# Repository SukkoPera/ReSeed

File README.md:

# ReSeed

ReSeed is an expansion card for the Commodore 16 and Plus/4 computers that allows interfacing the computer with a [MOS 6581 or 8580 Sound Interface Device](https://en.wikipedia.org/wiki/MOS_Technology_6581), the chip that is used to deliver audio on the Commodore 64.

It is based on [a design by Solder of Synergy](https://plus4world.powweb.com/hardware/Solders_SID_Card).

## Summary
Sounds from the C64 now for the Plus/4! Just plug the card into the Expansion Port! You can adjust the volume on the card. You can hear the sound over the Plus/4 audio or take it over a 3.5mm-Stereo-Cinch to a mixer or HiFi-Device. A 9-pin D-SUB connector allows connecting a 3<sup>rd</sup> (analog!) joystick or a proportional-mouse or (why not?) paddles!

*(Slight rewording of Solder's original description of the card.)*

## Design
ReSeed is derived from Solder's SIDcard, with a few enhancements.

### Modifications Introduced in V2
The focus for V2 was on reducing the output noise.

* New component values for the step-up voltage regulator: The values of some components were fine-tuned (again) in order to place the switching frequency of the step-up voltage converter way out of the audio band. These new values can also be retrofitted on a V1 board and will improve things dramatically (See [V1.1](https://github.com/SukkoPera/ReSeed/releases/tag/v1.1)).
* Alternative voltage step-up module: Cheap step-up voltage boost modules can now be used instead of the TL497-based circuit. Such modules, which can be easily sourced from Chinese portals, are much more modern and use a higher switching frequency, resulting in (near-)zero switching-induced noise. Using them also speeds up the assembly process, as many components can be skipped.
* Linear Regulator: If you are really paranoid about switching-induced noise, you can use the above alternatives as a first-stage voltage regulator and then make a second stage through a linear regulator, which should "eat" any remaining noise and provide the SID with very stable power.
* Separate grounds: A separate audio ground plane was introduced and connected to the signal ground plane through a single ferrite bead, preventing noise from spreading from the latter to the former. A second ferrite bead was inserted on the incoming +5V power rail in order to make it cleaner.
* Alternative BJT footprint: An alternative footprint for the output amplifier transistor was added, allowing for the mounting of the 2SC1815 BJT used in the original C64 audio circuit.
* SID clock delay circuit: This allows use of CD74HCT4520B chips in place of the CD4520B.
* Clock divider reset: Makes sure the SID clock always has the correct phase upon startup/reset.
* Short-circuit protection: In the original Solder design, a short-circuit can happen on the joystick port if it is written to. Series resistors were added in order to avoid this situation.

### Modifications Introduced in [V1](https://github.com/SukkoPera/ReSeed/releases/tag/v1)
* Supports both MOS 6581 and 8580 SIDs: this depends on mounting different components though, the board **cannot** be switched "on-the-fly", see [below](#Assembly).
* A volume control for the DigiFix was added and even a switch to completely bypass it.
* The output switch was removed: audio is automatically redirected to the Plus/4's EXT_AUDIO when nothing is connected to the output jack.
* The second stage of the amplifier was removed and the first stage modified so that it uses the same circuit and component values as the C64: the original card was known to introduce some distortion to the output signal as it was trying to amplify it, these days you can easily do better amplification outboard, so we chose to preserve sound fidelity.
* A decoupling capacitor was added close to every IC.
* The values for the step-up converter were recalculated in order to make the generated voltage less noisy and as ripple-free as possible.
* Last but not least, the design was documented and made open.

## Assembly
If you want to assemble a card, **please read the assembly notes on [the Wiki](https://github.com/SukkoPera/ReSeed/wiki) carefully or you might destroy your SID chip!**

### SID Replacements
Most SID replacements will not work correctly. This is because for technical reasons the clock that is provided to the SID has a lower frequency than what it gets on the C64 (~886 vs ~985 kHz). Most SID replacements do not use this clock signal at all and just assume C64 frequency (I guess), leading to incorrect data transfers. This is the case for the SwinSID firmware, for instance.  See below for a table of tested SID replacement devices.

| SID Device | Compatibility | Source | Notes |
|:---:|:---:|:---:|:---|
| [ARMSID](https://www.nobomi.cz/8bit/armsid/index_en.php) | Yes | [Root42](https://www.youtube.com/watch?v=OQfjMYeEfFY) | May have subtle incompatibility (detected during porting of config tool to +4), but unlikely to be seen in practise. |
| [SIDKick](https://github.com/frntc/SIDKick-pico) | In Progress | [SIDKick Pico Github](https://github.com/frntc/SIDKick-pico/discussions/36) | |
| [SwinSID](https://github.com/dmantione/swinsid) | No | SukkoPera | One report of compatibility, but no evidence provided. |
| BackSID | No | [BackBit Forums](https://forum.backbit.io/index.php?topic=1089.0) | Discontinued closed-source product; firmware unlikely to be patched. |
| [KungFuSID](https://github.com/Sgw32/KungFuSID) | No | SukkoPera |  |
| [PD-SID](https://uni64.com/shop/index.php?system=4&m=70&item_id=7536) | No | SteveGuidi | Firmware v191; no sound output and USB port inhibits proper seating in socket (obstructed by socketed CD74HCT4520E). |

## Games & Software
You can get images of the disks Solder used to ship with his SIDcard [here](https://plus4world.powweb.com/software/Synergy_Sidcard_Software). These will help making sure that the card works as intended.

[Here is also a list](https://plus4world.powweb.com/effects/SID_Support) of a lot of C16/+4 games and software supporting the card.

## Releases
If you want to get this board produced, you are recommended to get [the latest release](https://github.com/SukkoPera/ReSeed/releases) rather than the current git version, as the latter might be under development and is not guaranteed to be working.

Every release is accompanied by its Bill Of Materials (BOM) file and any relevant notes about it, which you are recommended to read carefully.

## Enclosure
A 3D-printable enclosure is currently available for this board, it was kindly contributed by [Starquake](https://www.forum64.de/wcf/index.php?user/17096-starquake/) and it is available in the [enclosure](./enclosure) folder.

Usage should be self-explanatory, just note that there are two slightly different versions depending on the SID model, as the one for the 8580 has an extra hole in the upper shell for the Digifix). You will probably have to bend the ferrites and capacitor at the bottom of the board a little to the side.

2x countersunk head screws M3x5mm will be required for assembly.

Please see [this thread on Forum64](https://www.forum64.de/index.php?thread/138918-sammelbestellung-reseed-sid-cartridge-f%C3%BCr-plus-4-und-c16/&postID=2125424#post2125424) for more information and printing recommendations.

[SteveGuidi](https://github.com/SteveGuidi) kindly contributed original-264-style labels for the completed cartridge.

## License
The ReSeed documentation, including the design itself, is copyright &copy; SukkoPera 2022-2023 and is licensed under the [Creative Commons Attribution-NonCommercial-ShareAlike 4.0 International License](https://creativecommons.org/licenses/by-nc-sa/4.0/).

This documentation is distributed *as is* and WITHOUT ANY EXPRESS OR IMPLIED WARRANTIES whatsoever with respect to its functionality, operability or use, including, without limitation, any implied warranties OF MERCHANTABILITY, SATISFACTORY QUALITY, FITNESS FOR A PARTICULAR PURPOSE or infringement. We expressly disclaim any liability whatsoever for any direct, indirect, consequential, incidental or special damages, including, without limitation, lost revenues, lost profits, losses resulting from business interruption or loss of data, regardless of the form of action or legal theory under which the liability may be asserted, even if advised of the possibility or likelihood of such damages.

## Support the Project
If you want to get some boards manufactured, you can get them from PCBWay through this link:

You get my gratitude and cheap, professionally-made and good quality PCBs, I get some credit that will help with this and [other projects](https://www.pcbway.com/project/member/shareproject/?bmbid=41100). You won't even have to worry about the various PCB options, it's all pre-configured for you!

Also, if you still have to register, [you can use this link](https://www.pcbway.com/setinvite.aspx?inviteid=41100) to get some bonus initial credit (and yield me some more).

You can also buy me a coffee if you want:

## Thanks
- Solder, for designing the original card and sharing its schematics.
- [Kinmami](https://github.com/kinmami) for his invaluable support
- Luca, Chronos and all the folks at [Plus/4 World](https://plus4world.powweb.com/forum) for helping with the troubleshooting
- [thireo](https://github.com/thireo) for the [3D model of the headphone jack](https://github.com/thireo/kicad-library)

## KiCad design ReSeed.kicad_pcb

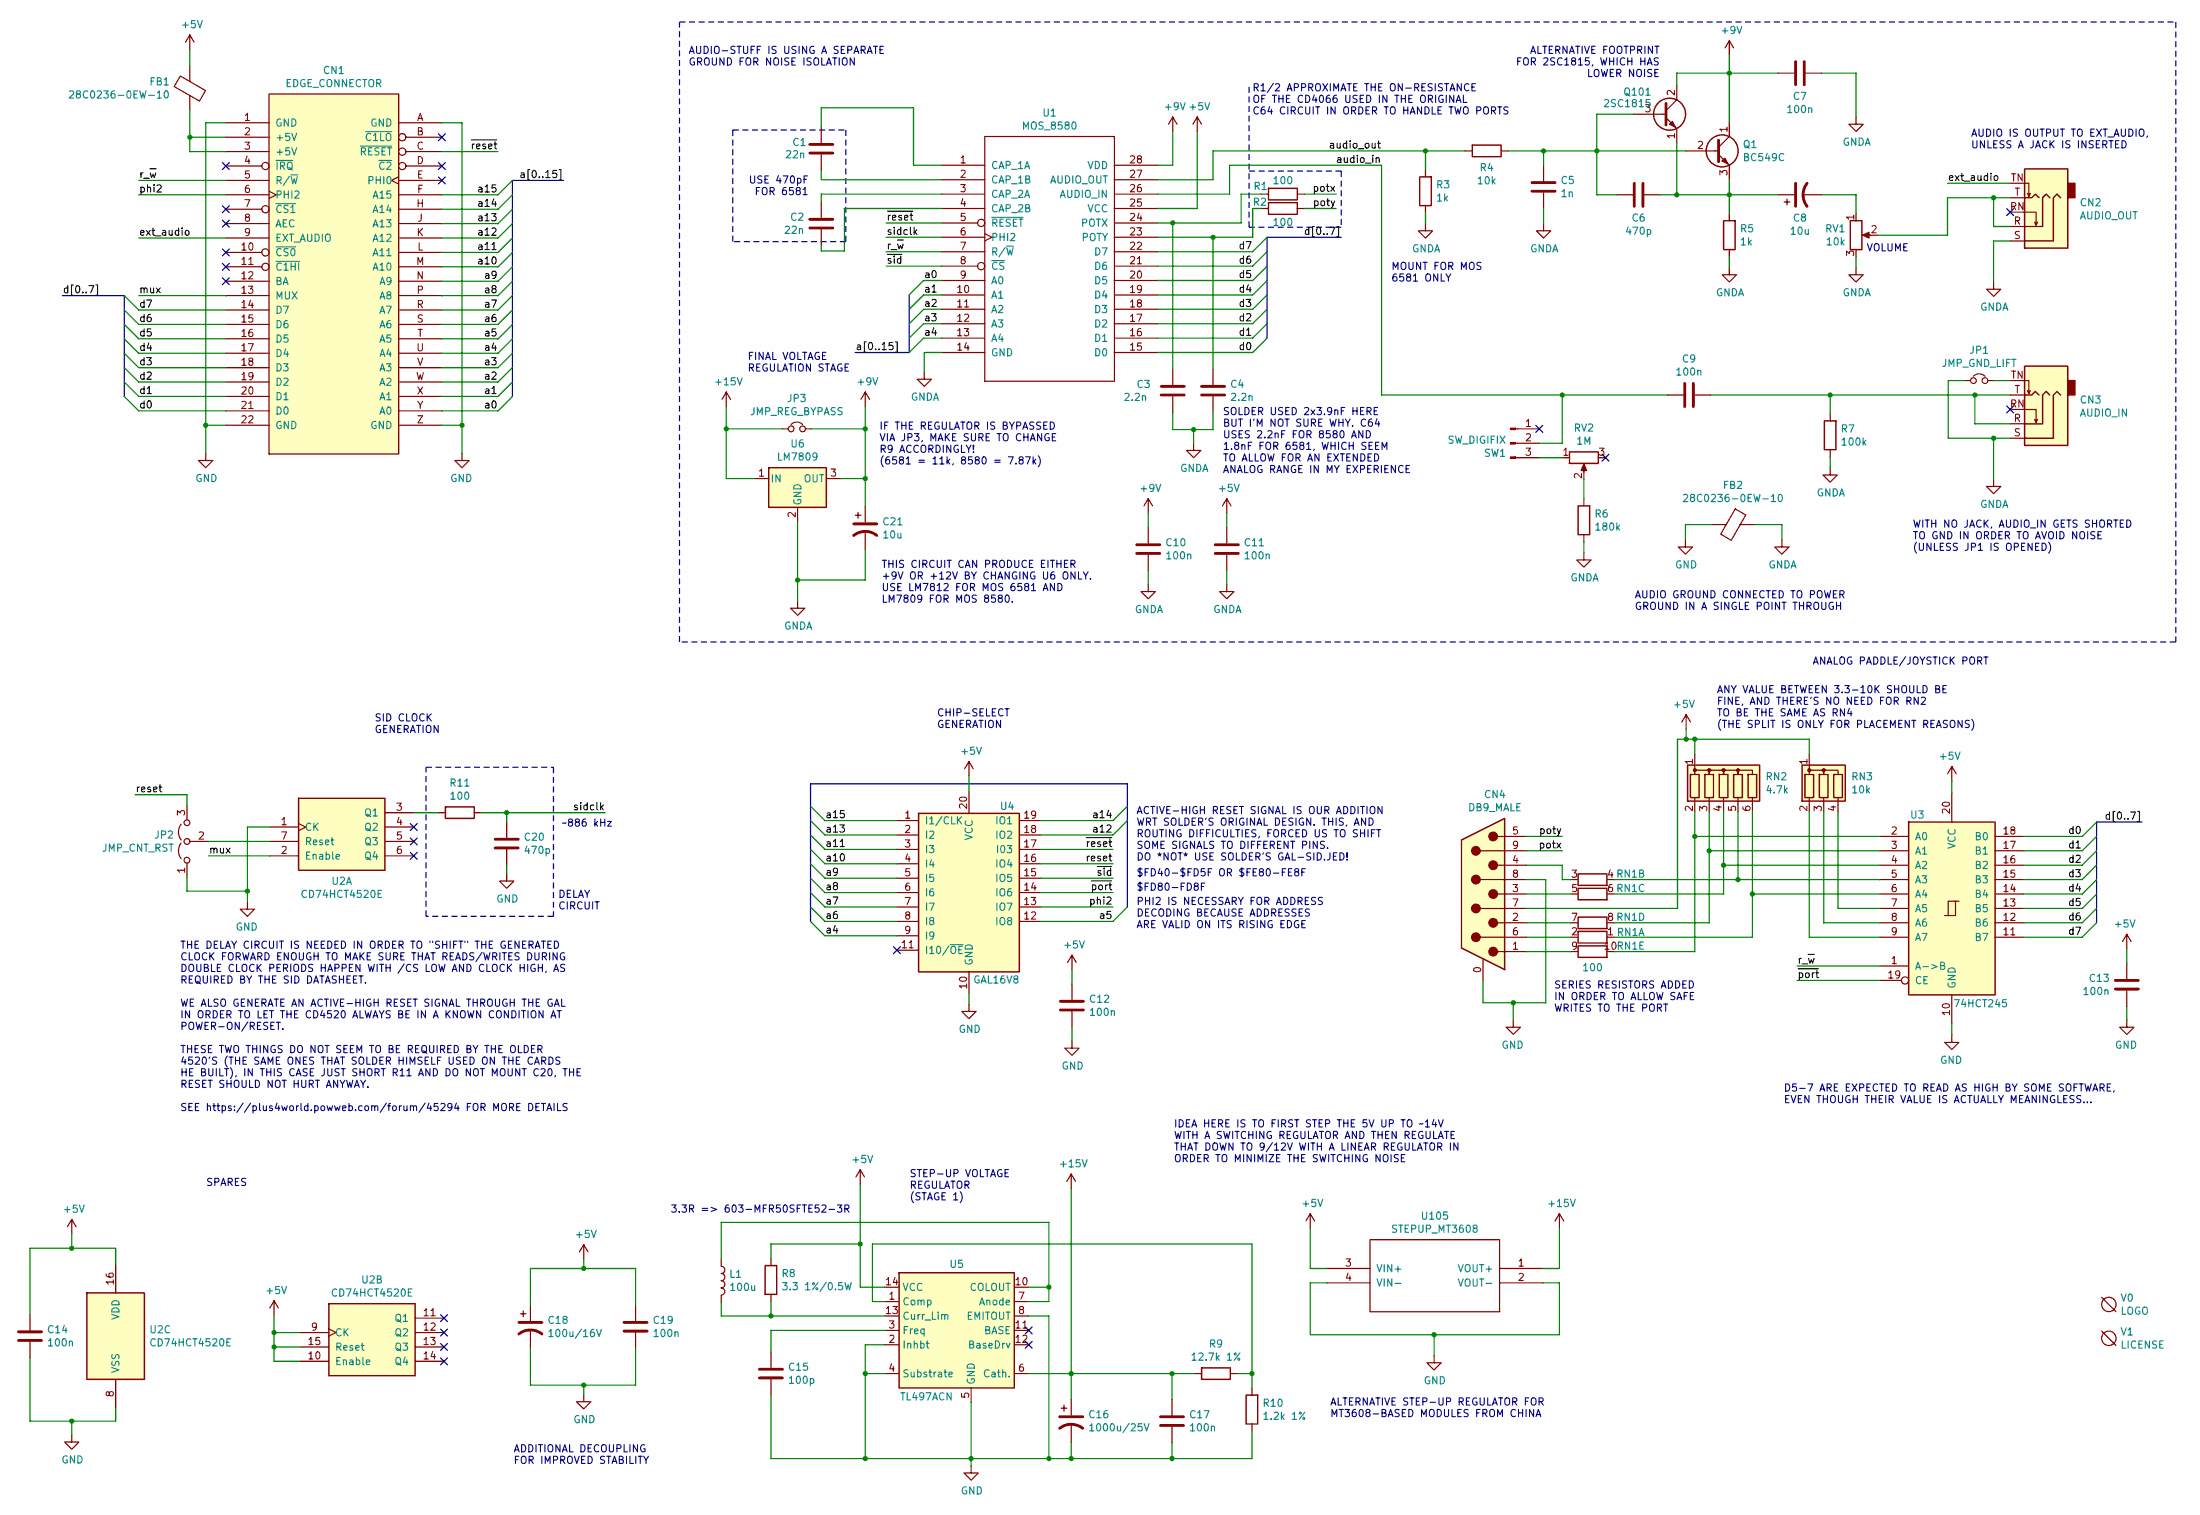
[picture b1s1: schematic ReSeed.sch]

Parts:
C1, C2: 22n; C_Disc_D7.0mm_W2.5mm_P5.00mm; MouserPN 810-FG28X7R1H223KNT0
C3, C4: 2.2n; C_Disc_D7.0mm_W2.5mm_P5.00mm; MouserPN 810-FG28C0G1H222JNT6
C5: 1n; C_Disc_D7.0mm_W2.5mm_P5.00mm; MouserPN 810-FG28C0G1H102JNT6
C6, C20: 470p; C_Disc_D7.0mm_W2.5mm_P5.00mm; MouserPN 810-FG28C0G1H471JNT6
C7, C9, C10, C11, C12, C13, C14, C17, C19: 100n; C_Disc_D7.0mm_W2.5mm_P5.00mm; MouserPN 810-FG28X7R1H104KNT0
C8, C21: 10u; CP_Radial_D5.0mm_P2.00mm; MouserPN 710-860010472002
C15: 100p; C_Disc_D7.0mm_W2.5mm_P5.00mm; MouserPN 810-FG28C0G1H101JNT6
C16: 1000u/25V; CP_Radial_D10.0mm_P5.00mm; MouserPN 710-860020475018
C18: 100u/16V; CP_Radial_D6.3mm_P2.50mm; MouserPN 710-860020573008
CN1: EDGE_CONNECTOR; C16-Exp-Port-44Pin
CN2: AUDIO_OUT; AudioJack_SJ1-3525N; MouserPN 490-SJ1-3525N
CN3: AUDIO_IN; AudioJack_SJ1-3525N; MouserPN 490-SJ1-3525N
CN4: DB9_MALE; DB_9M
FB1, FB2: 28C0236-0EW-10; L_Radial_D6.0mm_P4.00mm; MouserPN 875-28C0236-0EW-10
JP1: JMP_GND_LIFT; SolderJumper-2_P1.3mm_Bridged_RoundedPad1.0x1.5mm; MouserPN ---
JP2: JMP_CNT_RST; SolderJumper-3_P1.3mm_Open_RoundedPad1.0x1.5mm; MouserPN ---
JP3: JMP_REG_BYPASS; SolderJumper-2_P1.3mm_Open_RoundedPad1.0x1.5mm; MouserPN ---
L1: 100u; L_Radial_D8.7mm_P5.00mm_Fastron_07HCP; MouserPN 652-RLB0914-101KL
Q1: BC549C; TO-92_HandSolder; MouserPN 512-BC549CTA
Q101: 2SC1815; TO-92_HandSolder; MouserPN 610-2SC1815-GR
R1, R2, R11: 100; R_Axial_DIN0207_L6.3mm_D2.5mm_P10.16mm_Horizontal; MouserPN 660-MF1/4LCT52R101G
R3, R5: 1k; R_Axial_DIN0207_L6.3mm_D2.5mm_P10.16mm_Horizontal; MouserPN 603-MFR-25FBF52-1K
R4: 10k; R_Axial_DIN0207_L6.3mm_D2.5mm_P10.16mm_Horizontal; MouserPN 603-MFR-25FTF52-10K
R6: 180k; R_Axial_DIN0207_L6.3mm_D2.5mm_P10.16mm_Horizontal; MouserPN 603-MF0207FTE52-180K
R7: 100k; R_Axial_DIN0207_L6.3mm_D2.5mm_P10.16mm_Horizontal; MouserPN 603-MFR-25FBF52-100K
R8: 3.3 1%/0.5W; R_Axial_DIN0207_L6.3mm_D2.5mm_P10.16mm_Horizontal; MouserPN 603-MFR50SFTE52-3R3
R9: 12.7k 1%; R_Axial_DIN0207_L6.3mm_D2.5mm_P10.16mm_Horizontal; MouserPN 603-MFR-25FRF52-12K7
R10: 1.2k 1%; R_Axial_DIN0207_L6.3mm_D2.5mm_P10.16mm_Horizontal; MouserPN 603-MF0207FTE52-1K2
RN1: 100; R_Array_SIP10; MouserPN 652-4610X-2LF-100
RN2: 4.7k; R_Array_SIP6; MouserPN 652-4606X-1LF-4.7K
RN3: 10k; R_Array_SIP4; MouserPN 652-4604X-1LF-10K
RV1: 10k; Pot_Bourns_3306P; MouserPN 652-3306P-1-103
RV2: 1M; Pot_Bourns_3306P; MouserPN 652-3306P-1-105
SW1: SW_DIGIFIX; PinHeader_1x03_P2.54mm_Vertical
U1: MOS_8580; DIP-28_W15.24mm_Socket_LongPads; MouserPN :)
U2: CD74HCT4520E; DIP-16_W7.62mm_Socket_LongPads; MouserPN 595-CD74HCT4520E
U3: 74HCT245; DIP-20_W7.62mm_Socket_LongPads; MouserPN 595-SN74HCT245N
U4: GAL16V8; DIP-20_W7.62mm_Socket_LongPads; MouserPN 556-AF16V8B15PU
U5: TL497ACN; DIP-14_W7.62mm_Socket_LongPads; MouserPN 595-TL497ACNE4
U6: LM7809; TO-220-3_Vertical_Round; MouserPN 926-LM2940T-90/NOPB
U105: STEPUP_MT3608; ChineseUpstepperMT3608Style
V0: LOGO; Logo; MouserPN ---
V1: LICENSE; cc_by_nc_sa; MouserPN ---

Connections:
+5V: C11.1, C12.1, C13.1, C14.1, C18.1, C19.1, CN4.7, FB1.2, R8.1, RN2.1 (common), RN3.1 (common), U1.25 (VCC), U2.9 (CK), U2.10 (Enable), U2.15 (Reset), U2.16 (VDD), U3.20 (VCC), U4.20 (VCC), U5.14 (VCC), U105.3 (VIN+)
+9V: C7.2, C10.1, C21.1, JP3.2, Q1.1 (C), Q101.2 (C), U1.28 (VDD), U6.3 (OUT)
+15V: C16.1, C17.1, JP3.1, R9.2, U5.6 (Cath.), U6.1 (IN), U105.1 (VOUT+)
/a0: CN1.Y (A0), U1.9 (A0)
/a1: CN1.X (A1), U1.10 (A1)
/a2: CN1.W (A2), U1.11 (A2)
/a3: CN1.V (A3), U1.12 (A3)
/a4: CN1.U (A4), U1.13 (A4), U4.9 (I9)
/a5: CN1.T (A5), U4.12 (IO8)
/a6: CN1.S (A6), U4.8 (I8)
/a7: CN1.R (A7), U4.7 (I7)
/a8: CN1.P (A8), U4.6 (I6)
/a9: CN1.N (A9), U4.5 (I5)
/a10: CN1.M (A10), U4.4 (I4)
/a11: CN1.L (A11), U4.3 (I3)
/a12: CN1.K (A12), U4.18 (IO2)
/a13: CN1.J (A13), U4.2 (I2)
/a14: CN1.H (A14), U4.19 (IO1)
/a15: CN1.F (A15), U4.1 (I1/CLK)
/audio_in: C9.2, SW1.2, U1.26 (AUDIO_IN)
/audio_out: R3.2, R4.2, U1.27 (AUDIO_OUT)
/d0: CN1.21 (D0), U1.15 (D0), U3.18 (B0)
/d1: CN1.20 (D1), U1.16 (D1), U3.17 (B1)
/d2: CN1.19 (D2), U1.17 (D2), U3.16 (B2)
/d3: CN1.18 (D3), U1.18 (D3), U3.15 (B3)
/d4: CN1.17 (D4), U1.19 (D4), U3.14 (B4)
/d5: CN1.16 (D5), U1.20 (D5), U3.13 (B5)
/d6: CN1.15 (D6), U1.21 (D6), U3.12 (B6)
/d7: CN1.14 (D7), U1.22 (D7), U3.11 (B7)
/ext_audio: CN1.9 (EXT_AUDIO), CN2.TN
/mux: CN1.13 (MUX), U2.2 (Enable)
/phi2: CN1.6 (PHI2), U4.13 (IO7)
/potx: CN4.9, R1.1
/poty: CN4.5, R2.1
/r_~w: CN1.5 (R/~W), U1.7 (R/~W), U3.1 (A->B)
/reset: JP2.3 (B), U4.16 (IO4)
/sidclk: C20.1, R11.1, U1.6 (PHI2)
/~port: U3.19 (CE), U4.14 (IO6)
/~reset: CN1.C (~RESET), U1.5 (~RESET), U4.17 (I03)
/~sid: U1.8 (~CS), U4.15 (IO5)
GND: C12.2, C13.2, C14.2, C15.2, C16.2, C17.2, C18.2, C19.2, C20.2, CN1.1 (GND), CN1.22 (GND), CN1.A (GND), CN1.Z (GND), CN4.0 (PAD), CN4.8, FB2.2, JP2.1 (A), R10.1, U2.1 (CK), U2.8 (VSS), U3.10 (GND), U4.10 (GND), U5.2 (Inhbt), U5.4 (Substrate), U5.5 (GND), U5.8 (EMITOUT), U105.2 (VOUT-), U105.4 (VIN-)
GNDA: C3.2, C4.2, C5.2, C7.1, C10.2, C11.2, C21.2, CN2.S, CN3.S, FB2.1, JP1.1, R3.1, R5.1, R6.1, R7.1, RV1.3, U1.14 (GND), U6.2 (GND)
unnamed: C1.1, U1.1 (CAP_1A)
unnamed: C1.2, U1.2 (CAP_1B)
unnamed: C2.1, U1.3 (CAP_2A)
unnamed: C2.2, U1.4 (CAP_2B)
unnamed: C3.1, R1.2, U1.24 (POTX)
unnamed: C4.1, R2.2, U1.23 (POTY)
unnamed: C5.1, C6.2, Q1.2 (B), Q101.3 (B), R4.1
unnamed: C6.1, C8.1, Q1.3 (E), Q101.1 (E), R5.2
unnamed: C8.2, RV1.1
unnamed: C9.1, CN3.R, CN3.T, R7.2
unnamed: C15.1, U5.3 (Freq)
unnamed: CN1.2 (+5V), CN1.3 (+5V), FB1.1
unnamed: CN2.R, CN2.T, RV1.2
unnamed: CN3.TN, JP1.2
unnamed: CN4.1, RN1.9 (R5.1)
unnamed: CN4.2, RN1.7 (R4.1)
unnamed: CN4.3, RN1.5 (R3.1)
unnamed: CN4.4, RN1.3 (R2.1)
unnamed: CN4.6, RN1.2 (R1.2)
unnamed: JP2.2 (C), U2.7 (Reset)
unnamed: L1.1, U5.7 (Anode), U5.10 (COLOUT)
unnamed: L1.2, R8.2, U5.13 (Curr_Lim)
unnamed: R6.2, RV2.2
unnamed: R9.1, R10.2, U5.1 (Comp)
unnamed: R11.2, U2.3 (Q1)
unnamed: RN1.1 (R1.1), RN2.6 (R5), U3.6 (A4)
unnamed: RN1.4 (R2.2), RN2.5 (R4), U3.5 (A3)
unnamed: RN1.6 (R3.2), RN2.4 (R3), U3.4 (A2)
unnamed: RN1.8 (R4.2), RN2.3 (R2), U3.3 (A1)
unnamed: RN1.10 (R5.2), RN2.2 (R1), U3.2 (A0)
unnamed: RN3.2 (R1), U3.9 (A7)
unnamed: RN3.3 (R2), U3.8 (A6)
unnamed: RN3.4 (R3), U3.7 (A5)
unnamed: RV2.1, SW1.3

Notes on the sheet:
STEP-UP VOLTAGE REGULATOR (STAGE 1)
ANALOG PADDLE/JOYSTICK PORT
VOLUME
SPARES
D5-7 ARE EXPECTED TO READ AS HIGH BY SOME SOFTWARE, EVEN THOUGH THEIR VALUE IS ACTUALLY MEANINGLESS...
ALTERNATIVE FOOTPRINT FOR 2SC1815, WHICH HAS LOWER NOISE
WITH NO JACK, AUDIO_IN GETS SHORTED TO GND IN ORDER TO AVOID NOISE (UNLESS JP1 IS OPENED)
USE 470pF FOR 6581
THIS CIRCUIT CAN PRODUCE EITHER +9V OR +12V BY CHANGING U6 ONLY. USE LM7812 FOR MOS 6581 AND LM7809 FOR MOS 8580.
ADDITIONAL DECOUPLING FOR IMPROVED STABILITY
AUDIO IS OUTPUT TO EXT_AUDIO, UNLESS A JACK IS INSERTED
MOUNT FOR MOS 6581 ONLY
SID CLOCK GENERATION
DELAY CIRCUIT
THE DELAY CIRCUIT IS NEEDED IN ORDER TO "SHIFT" THE GENERATED CLOCK FORWARD ENOUGH TO MAKE SURE THAT READS/WRITES DURING DOUBLE CLOCK PERIODS HAPPEN WITH /CS LOW AND CLOCK HIGH, AS REQUIRED BY THE SID DATASHEET. WE ALSO GENERATE AN ACTIVE-HIGH RESET SIGNAL THROUGH THE GAL IN ORDER TO LET THE CD4520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
~~886 kHz
SERIES RESISTORS ADDED IN ORDER TO ALLOW SAFE WRITES TO THE PORT
ACTIVE-HIGH RESET SIGNAL IS OUR ADDITION WRT SOLDER'S ORIGINAL DESIGN. THIS, AND ROUTING DIFFICULTIES, FORCED US TO SHIFT SOME SIGNALS TO DIFFERENT PINS. DO *NOT* USE SOLDER'S GAL-SID.JED!
PHI2 IS NECESSARY FOR ADDRESS DECODING BECAUSE ADDRESSES ARE VALID ON ITS RISING EDGE
$FD80-FD8F
$FD40-$FD5F OR $FE80-FE8F
CHIP-SELECT GENERATION
ALTERNATIVE STEP-UP REGULATOR FOR MT3608-BASED MODULES FROM CHINA
AUDIO-STUFF IS USING A SEPARATE GROUND FOR NOISE ISOLATION
AUDIO GROUND CONNECTED TO POWER GROUND IN A SINGLE POINT THROUGH
IDEA HERE IS TO FIRST STEP THE 5V UP TO ~~14V WITH A SWITCHING REGULATOR AND THEN REGULATE THAT DOWN TO 9/12V WITH A LINEAR REGULATOR IN ORDER TO MINIMIZE THE SWITCHING NOISE
FINAL VOLTAGE REGULATION STAGE
IF THE REGULATOR IS BYPASSED VIA JP3, MAKE SURE TO CHANGE R9 ACCORDINGLY! (6581 = 11k, 8580 = 7.87k)
ANY VALUE BETWEEN 3.3-10K SHOULD BE FINE, AND THERE'S NO NEED FOR RN2 TO BE THE SAME AS RN4 (THE SPLIT IS ONLY FOR PLACEMENT REASONS)
3.3R => 603-MFR50SFTE52-3R
SOLDER USED 2x3.9nF HERE BUT I'M NOT SURE WHY. C64 USES 2.2nF FOR 8580 AND 1.8nF FOR 6581, WHICH SEEM TO ALLOW FOR AN EXTENDED ANALOG RANGE IN MY EXPERIENCE
R1/2 APPROXIMATE THE ON-RESISTANCE OF THE CD4066 USED IN THE ORIGINAL C64 CIRCUIT IN ORDER TO HANDLE TWO PORTS

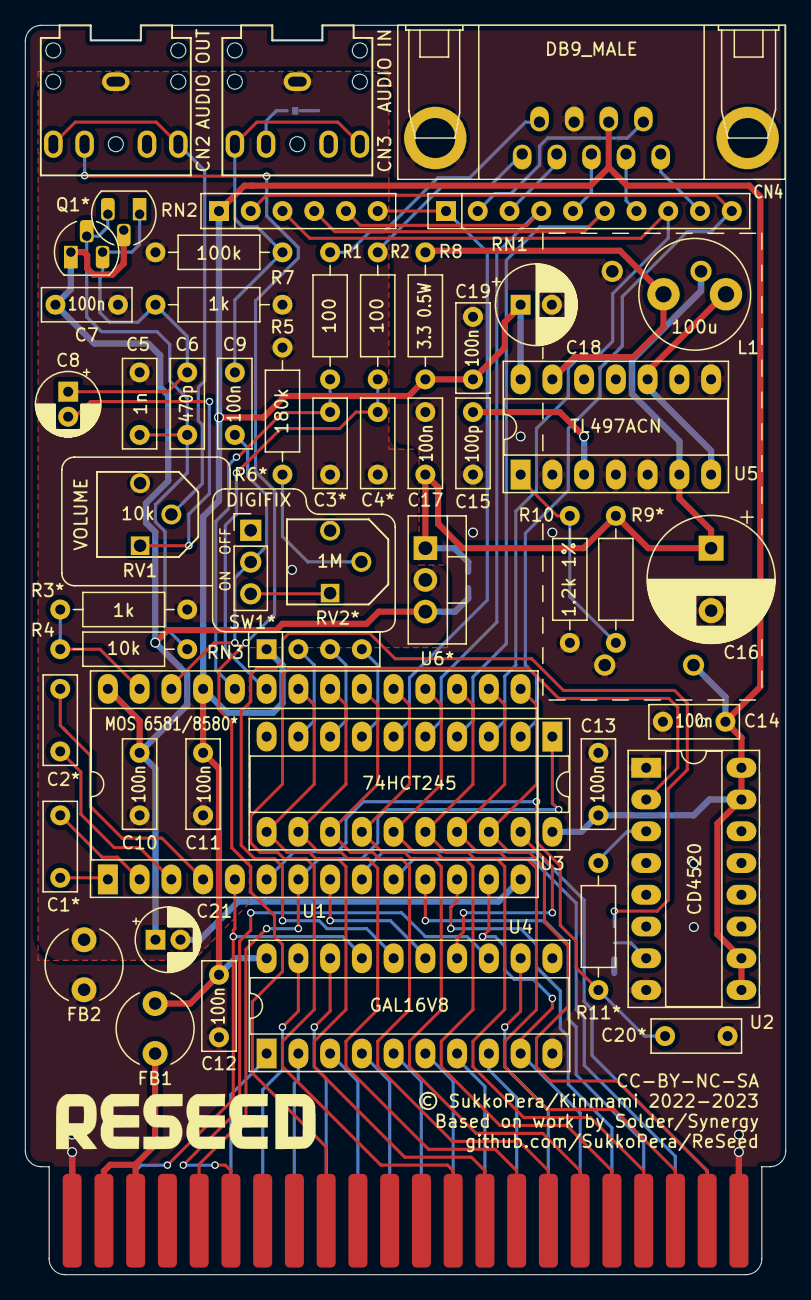
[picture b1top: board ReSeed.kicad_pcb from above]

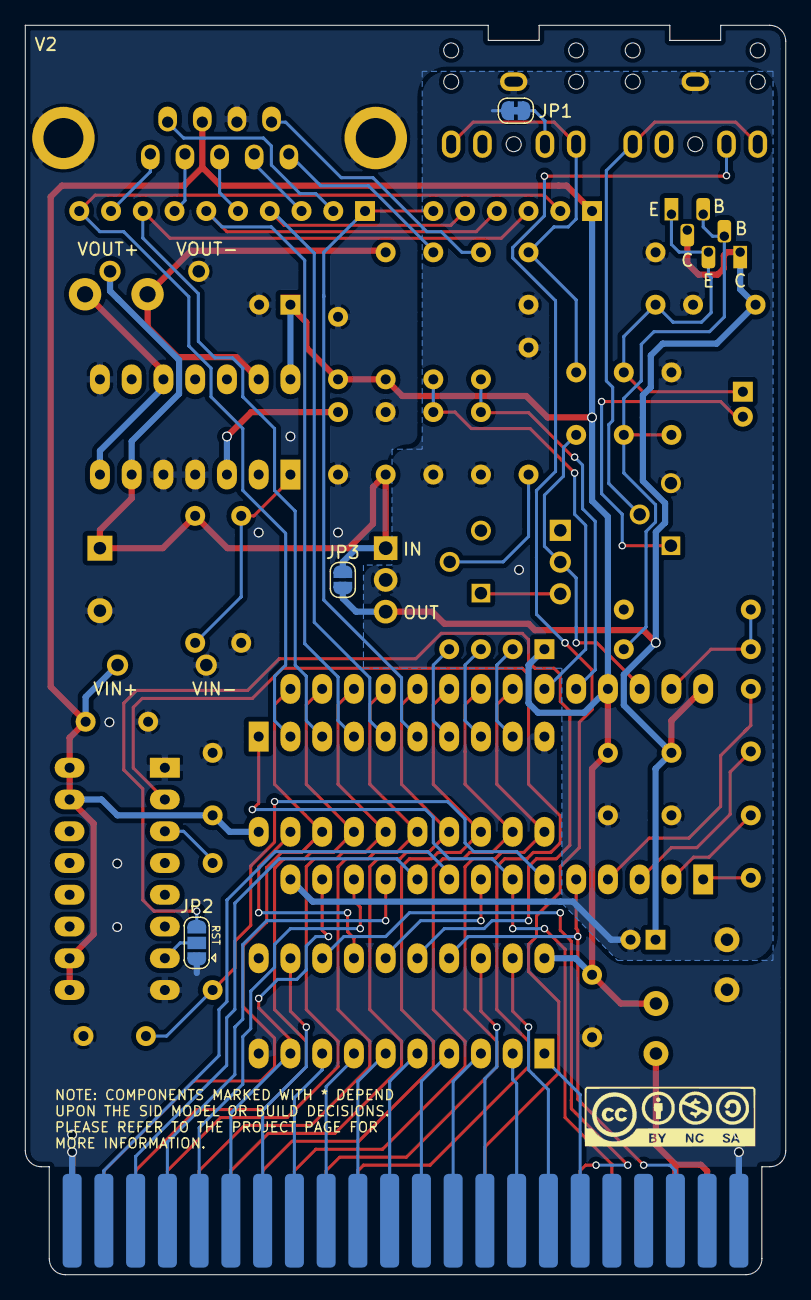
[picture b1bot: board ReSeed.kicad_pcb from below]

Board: 2 copper layers, 60.8 x 99.9 mm, 59 parts (4 on the bottom side), 76 nets.

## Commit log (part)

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2022-02-09 First commit Schematics and rough component placement complete
2022-02-10 Back side complete?
2022-02-11 Top routing in progress
2022-02-11 Initial 1:1 replica complete
2022-02-12 Fix overlapping track
2022-02-12 Switch to radial inductor and make boards slightly shorter
2022-02-12 Make board shorter than 10cm
2022-02-12 Switch to ground plane and lots of improvements
2022-02-13 Tidy up silkscreen
2022-02-13 Move some components around
2022-02-16 Rework power circuit
2022-02-16 Add logo and license
2022-02-16 Add MOS 6582 datasheet
2022-02-16 Work in progress
2022-02-16 Almost there...
2022-02-19 In Funken versunken
2022-02-19 Und bin ich In Wasser verbrandt
2022-02-19 Stehe ich in Flammen
2022-02-20 Feuer und Wasser
2022-02-20 Ready?
2022-02-21 Add note about R3
2022-02-23 Improve decoupling on U5
2022-03-05 Reroute some tracks around DC/DC converter
2022-03-20 Reroute one more track to make ground more solid around DC-DC converter
2022-03-20 Change headphone connectors
2022-03-20 Change pots
2022-03-20 Fix silkscreen
2022-10-22 Rename ReSeedGal.pld to ReSeed.pld
2022-10-22 Add pictures of Chronos's SIDcard
2022-10-22 Update GAL equations for CD4520 reset hack
    WARNING: Requires modifications to V1 board!
2022-10-24 Add link to pictures folder
2022-10-24 Move some tracks
2022-10-24 Add series resistors on joystick port
2022-10-24 Reset the 4520 with /RESET This required a lot of shuffling of the GAL pins.
2022-10-24 Improve positioning of some tracks/components/labels
2022-10-24 Add clock delay circuit See https://plus4world.powweb.com/forum/45294 for more information
2022-10-24 Update GAL equations for V2 board
2022-10-24 Fix BJT P/N
2022-10-24 Add renders and boards link
2022-10-24 Add note on software
2022-10-24 Add links to collaborators
2022-11-06 WIP - Add footprint for MT3608-based regulator modules from China
2022-11-06 Routing completed - Need @kinmami's opinion on it
2022-11-06 Move track
2022-11-08 Make counter reset DISABLABLE
2022-11-11 Try separating signal and power grounds
2022-11-11 Only missing ferrites
2022-11-12 Add ferrites on power lines
2022-11-12 Use 2-stage step-up voltage regulation @kinmami: You owe me a monument
2022-11-12 Silkscreen fixes
2022-11-12 Add bypass jumper for 2nd regulator stage
2022-11-12 Change 3D model of ferrites
2022-11-12 Reverse pots so that volume grows clockwise
2022-11-12 R8 -> 4.7R, C16 -> 1000u This fixes a lot of the background noise!
2022-11-12 Fix track leading to LDO
2022-11-12 Final touches on silkscreen
2022-11-13 Update notes, P/Ns, schematics, docs, etc.
2022-11-13 Minor grounding improvements
2022-12-08 Fix some part numbers
2022-12-09 Add alternative footprint for 2SC1815 transistor
2022-12-09 Undo pot reversal
2022-12-09 C15 -> 100pF
2022-12-09 Make Chinese step-up module pins closer
2022-12-11 Correct P/Ns of resistor networks
2023-01-14 Correct BJT terminal labels Grrrrrrrrrrrrrrr!!!
2023-01-14 R8 -> 3.3 ohm
2023-01-15 Make D5-7 high on joystick reads Solder's joyport tester seems to require this, sigh...
2023-01-15 Update copyright year
2023-01-15 Add note on C3/4
2023-01-15 Reduce output noise C15 -> 100p, R8 -> 3.3, L1 -> 100u
2023-01-15 Add P/N for Q101
2023-01-15 Add P/Ns
2023-01-15 Fix typo
2023-08-12 Make C3/4 SID-model-dependent
2023-08-12 Update renders and README
2023-08-12 Add list of V2 modifications
2023-08-12 BOM fixes for #1 and README update
2024-06-01 Fix confusion about R3 - See #3
2024-06-01 Add enclosure, thanks Starquake!
2025-06-05 Created cartridge labels for the enclosure in the style of existing 264-series cartridges
2026-02-13 Change coffee donation image link in README
    Updated the coffee donation link image in the README.
2026-03-03 Ready for 44-pin version
2026-04-22 Update README.md
    Added compatibility table for SID replacement devices.
2026-04-22 Update README.md
    Updated compatibility table with feedback.
2026-04-22 Update README.md
    Added KungFuSID compatibility notes.
2026-04-23 Add GitHub badges to README
    Added badges for GitHub release information and commit stats.

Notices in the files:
ReSeed.kicad_pcb:
Licensed under CC BY-NC-SA 4.0
© SukkoPera/Kinmami 2022-2023
parts and their libraries:
LICENSE: Value
